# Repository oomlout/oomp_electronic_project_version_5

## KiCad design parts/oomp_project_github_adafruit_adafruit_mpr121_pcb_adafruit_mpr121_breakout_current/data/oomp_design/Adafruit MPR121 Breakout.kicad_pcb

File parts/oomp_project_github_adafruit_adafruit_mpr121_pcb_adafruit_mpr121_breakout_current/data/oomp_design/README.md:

# OOMP KiCad design copy

Open `Adafruit MPR121 Breakout.kicad_pro` (or the `.kicad_pcb` / `.kicad_sch`) in KiCad. Local OOMP libraries are under `libraries/`. Original inputs are preserved in [../original/](../original/).

Only verified unchanged installed KiCad defaults were renamed. Modified, custom, unmatched and unavailable items remain unchanged. Soldering variants are never swapped during conversion. Existing pad coordinates, nets and UUIDs are preserved.

See [conversion_report.yaml](conversion_report.yaml) for every conversion and skip. Copy this directory before editing; regeneration refuses to overwrite edited design files.

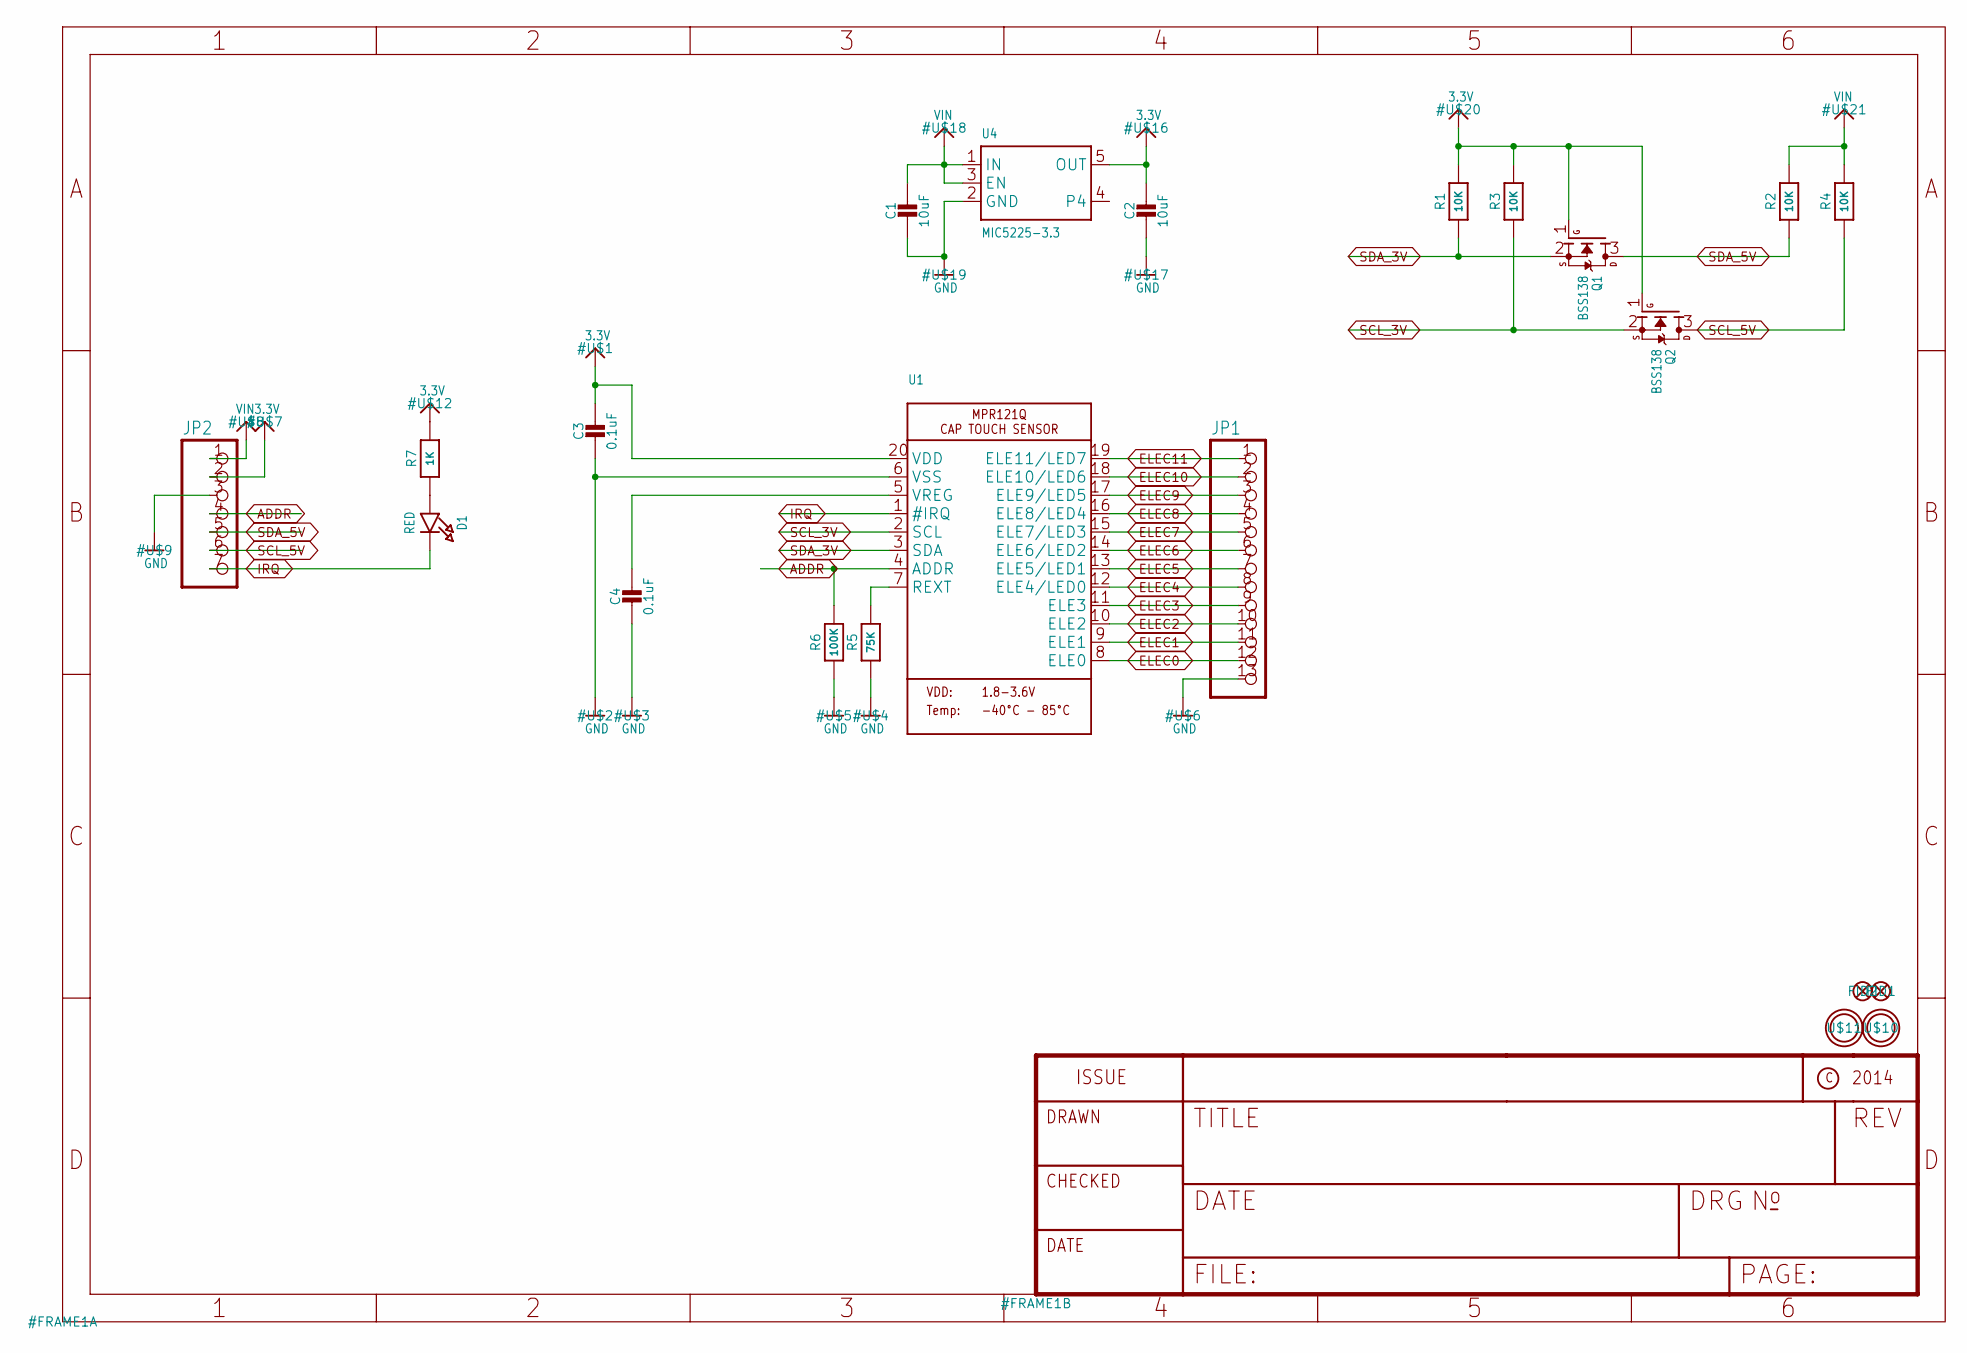
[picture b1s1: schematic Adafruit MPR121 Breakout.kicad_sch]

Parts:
C1, C2: 10uF; 0805-NO
C3: 0.1uF; 0805_10MGAP
C4: 0.1uF; 0805-NO
D1: RED; CHIPLED_0805_NOOUTLINE
FID1, FID2: FIDUCIAL""; FIDUCIAL_1MM
JP1: HEADER-1X13; 1X13_ROUND_70
JP2: HEADER-1X770MIL; 1X07_ROUND_70
Q1, Q2: BSS138; SOT23-WIDE
R1, R2, R3, R4: 10K; 0805-NO
R5: 75K; 0805-NO
R6: 100K; 0805-NO
R7: 1K; 0805-NO
U1: MPR121Q; QFN20_3MM_NOTHERMAL
U4: MIC5225-3.3; SOT23-5
U$10, U$11: MOUNTINGHOLE2.5; MOUNTINGHOLE_2.5_PLATED

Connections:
3.3V: C2.1, C3.1, JP2.2, Q1.1 (G), Q2.1 (G), R1.2, R3.2, R7.2, U1.20 (VDD), U4.5 (OUT)
ADDR: JP2.4, R6.2, U1.4 (ADDR)
ELEC0: JP1.12, U1.8 (ELE0)
ELEC1: JP1.11, U1.9 (ELE1)
ELEC2: JP1.10, U1.10 (ELE2)
ELEC3: JP1.9, U1.11 (ELE3)
ELEC4: JP1.8, U1.12 (ELE4/LED0)
ELEC5: JP1.7, U1.13 (ELE5/LED1)
ELEC6: JP1.6, U1.14 (ELE6/LED2)
ELEC7: JP1.5, U1.15 (ELE7/LED3)
ELEC8: JP1.4, U1.16 (ELE8/LED4)
ELEC9: JP1.3, U1.17 (ELE9/LED5)
ELEC10: JP1.2, U1.18 (ELE10/LED6)
ELEC11: JP1.1, U1.19 (ELE11/LED7)
GND: C1.2, C2.2, C3.2, C4.2, JP1.13, JP2.3, R5.1, R6.1, U1.6 (VSS), U4.2 (GND)
IRQ: D1.C, JP2.7, U1.1 (#IRQ)
unnamed: D1.A, R7.1
unnamed: C4.1, U1.5 (VREG)
unnamed: R5.2, U1.7 (REXT)
SCL_3V: Q2.2 (S), R3.1, U1.2 (SCL)
SCL_5V: JP2.6, Q2.3 (D), R4.1
SDA_3V: Q1.2 (S), R1.1, U1.3 (SDA)
SDA_5V: JP2.5, Q1.3 (D), R2.1
VIN: C1.1, JP2.1, R2.2, R4.2, U4.1 (IN), U4.3 (EN)

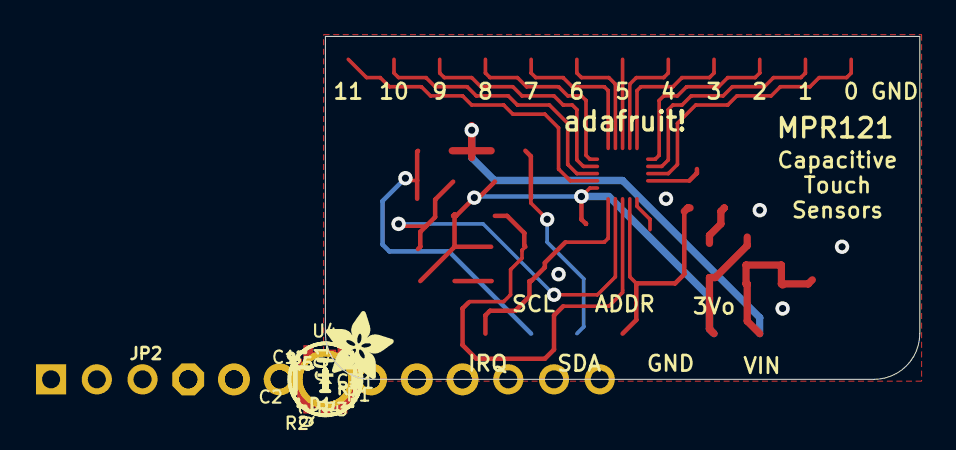
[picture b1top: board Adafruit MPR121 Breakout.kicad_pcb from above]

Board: 2 copper layers, 33.0 x 19.1 mm, 23 parts (0 on the bottom side), 24 nets.

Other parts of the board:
U$14: ADAFRUIT_3.5MM

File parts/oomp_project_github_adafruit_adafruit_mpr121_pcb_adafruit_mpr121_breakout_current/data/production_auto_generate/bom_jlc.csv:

Comment,Designator,Footprint,LCSC Part #
,JP2,Adafruit MPR121 Breakout-import-fps:1X07_ROUND_70,C7501585
,JP1,Adafruit MPR121 Breakout-import-fps:1X13_ROUND_70,C2894936
,U$14,Adafruit MPR121 Breakout-import-fps:ADAFRUIT_3.5MM,
,U1,Adafruit MPR121 Breakout-import-fps:QFN20_3MM_NOTHERMAL,
0.1uF,C4,Adafruit MPR121 Breakout-import-fps:0805-NO,
0.1uF,C3,Adafruit MPR121 Breakout-import-fps:0805_10MGAP,
100K,R6,Adafruit MPR121 Breakout-import-fps:0805-NO,C149504
10K,"R1,R2,R3,R4",Adafruit MPR121 Breakout-import-fps:0805-NO,C17414
10uF,"C1,C2",Adafruit MPR121 Breakout-import-fps:0805-NO,
1K,R7,Adafruit MPR121 Breakout-import-fps:0805-NO,C17513
75K,R5,Adafruit MPR121 Breakout-import-fps:0805-NO,C17819
BSS138,"Q1,Q2",Adafruit MPR121 Breakout-import-fps:SOT23-WIDE,C52895
MIC5225-3.3,U4,Adafruit MPR121 Breakout-import-fps:SOT23-5,
RED,D1,Adafruit MPR121 Breakout-import-fps:CHIPLED_0805_NOOUTLINE,

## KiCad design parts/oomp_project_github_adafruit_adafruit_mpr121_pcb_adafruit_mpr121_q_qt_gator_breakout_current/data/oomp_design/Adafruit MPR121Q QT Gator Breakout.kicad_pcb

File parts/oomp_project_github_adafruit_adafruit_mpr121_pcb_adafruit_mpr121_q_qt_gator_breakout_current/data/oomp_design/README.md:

# OOMP KiCad design copy

Open `Adafruit MPR121Q QT Gator Breakout.kicad_pro` (or the `.kicad_pcb` / `.kicad_sch`) in KiCad. Local OOMP libraries are under `libraries/`. Original inputs are preserved in [../original/](../original/).

Only verified unchanged installed KiCad defaults were renamed. Modified, custom, unmatched and unavailable items remain unchanged. Soldering variants are never swapped during conversion. Existing pad coordinates, nets and UUIDs are preserved.

See [conversion_report.yaml](conversion_report.yaml) for every conversion and skip. Copy this directory before editing; regeneration refuses to overwrite edited design files.

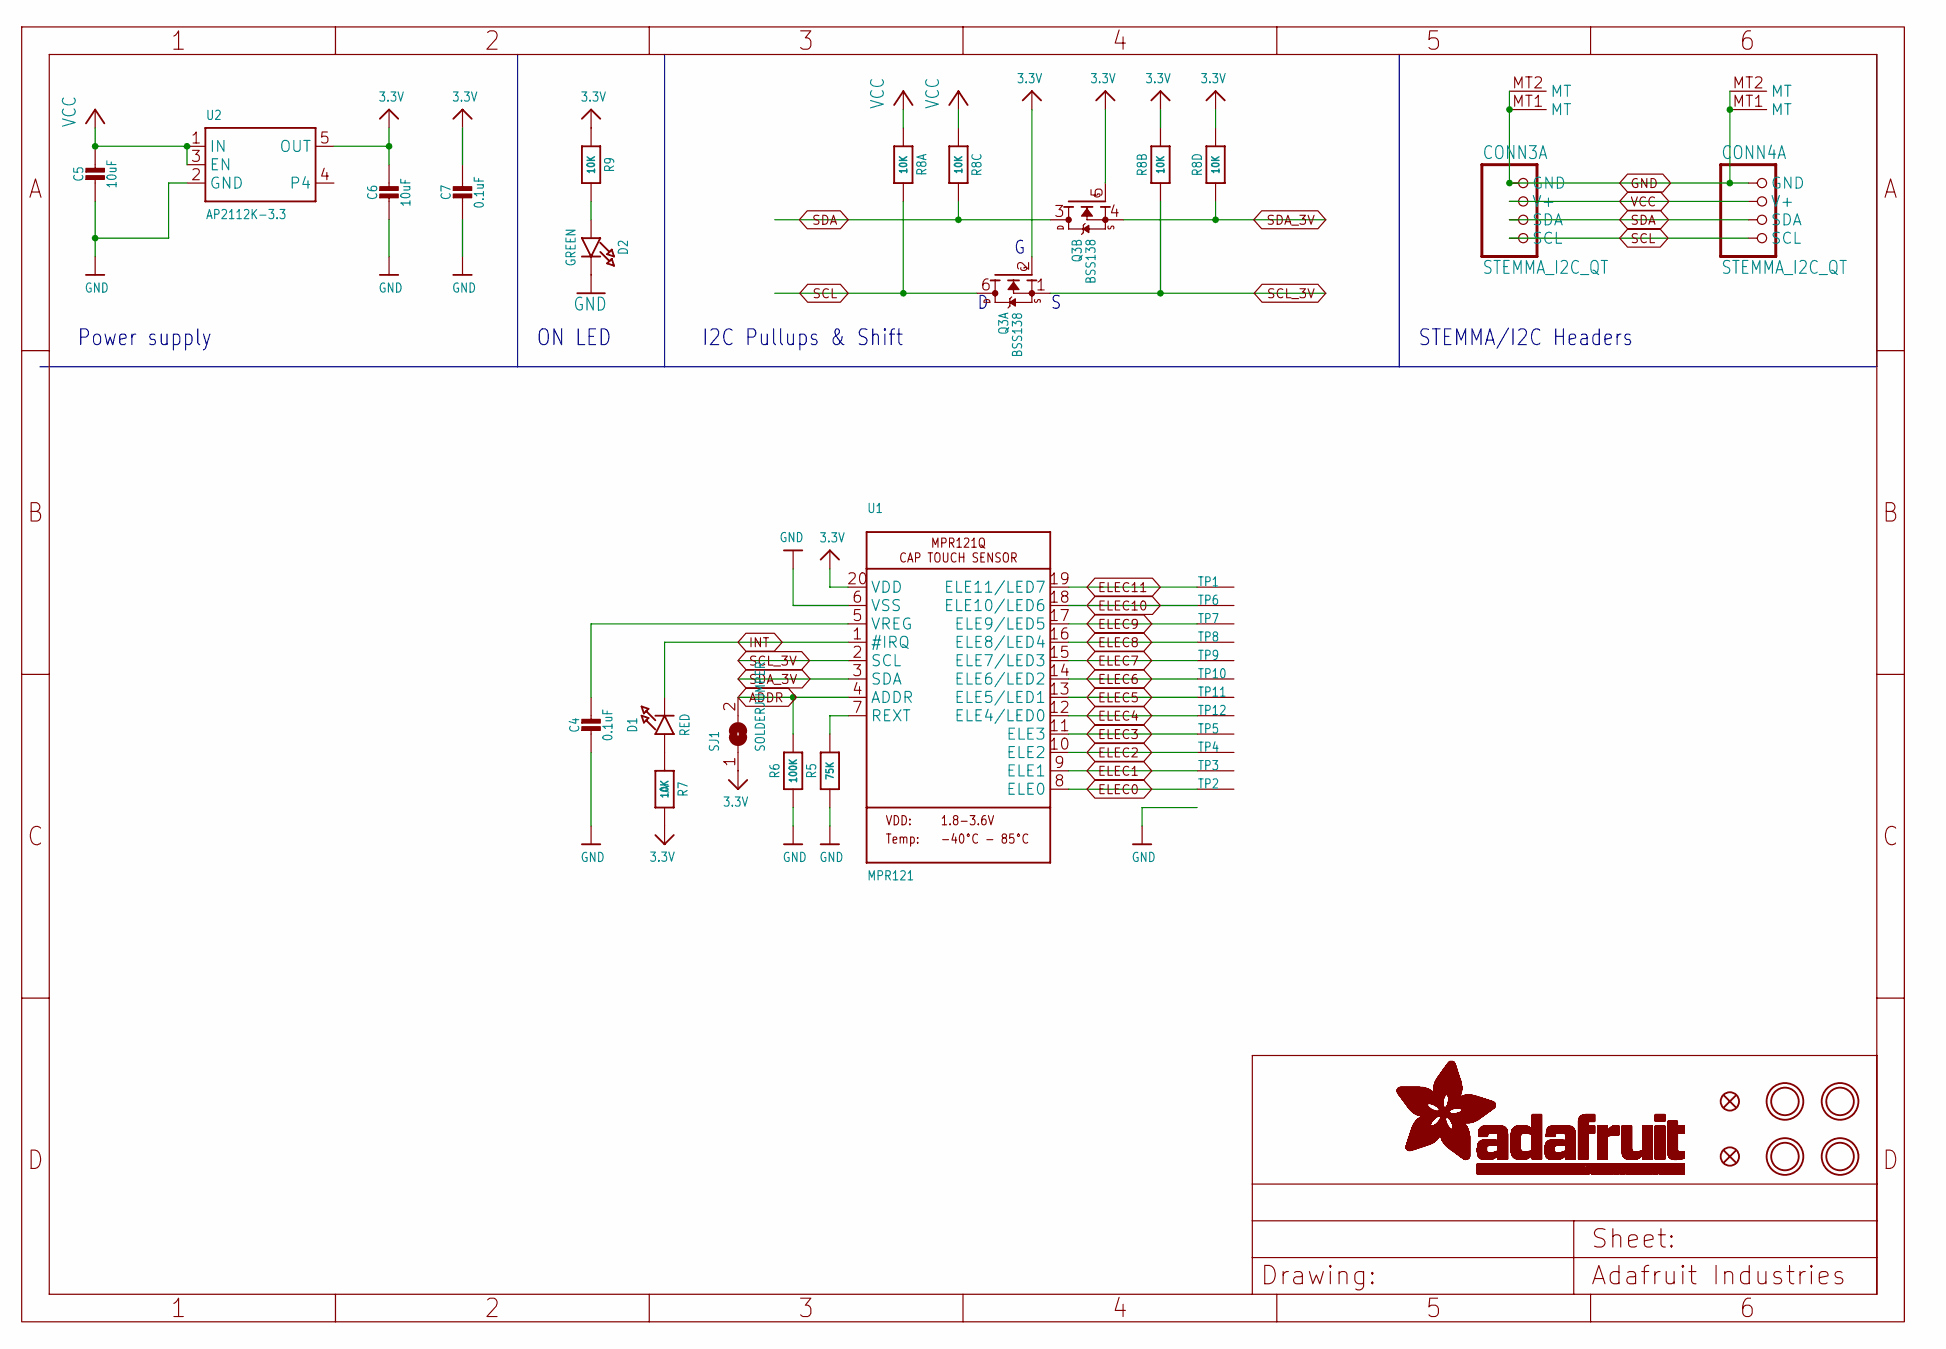
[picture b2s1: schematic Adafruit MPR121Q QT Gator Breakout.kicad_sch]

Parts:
C4, C7: 0.1uF; 0603-NO
C5, C6: 10uF; 0805-NO
CONN3, CONN4: STEMMA_I2C_QT; JST_SH4
D1: RED; CHIPLED_0603_NOOUTLINE
D2: GREEN; CHIPLED_0603_NOOUTLINE
FID3, FID4: FIDUCIAL_1MM
Q3: BSS138; SOT363
R5: 75K; 0603-NO
R6: 100K; 0603-NO
R7, R9: 10K; 0603-NO
R8: 10K; RESPACK_4X0603
SJ1: SOLDERJUMPER; SOLDERJUMPER_ARROW_NOPASTE
TP1, TP2, TP3, TP4, TP5, TP6, TP7, TP8, TP9, TP10, TP11, TP12: SEWTAPPCB_ALLIGATOR; PCB_ALLI
U1: MPR121; QFN20_3MM_NOTHERMAL
U2: AP2112K-3.3; SOT23-5
U$7, U$8, U$34, U$35: MOUNTINGHOLE2.5; MOUNTINGHOLE_2.5_PLATED

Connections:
3.3V: C6.1, C7.1, Q3.2 (G), Q3.5 (G), R7.2, R8.2 (1), R8.4 (1), R9.1, SJ1.1, U1.20 (VDD), U2.5 (OUT)
ADDR: R6.2, SJ1.2, U1.4 (ADDR)
ELEC0: TP2.P$1, U1.8 (ELE0)
ELEC1: TP3.P$1, U1.9 (ELE1)
ELEC2: TP4.P$1, U1.10 (ELE2)
ELEC3: TP5.P$1, U1.11 (ELE3)
ELEC4: TP12.P$1, U1.12 (ELE4/LED0)
ELEC5: TP11.P$1, U1.13 (ELE5/LED1)
ELEC6: TP10.P$1, U1.14 (ELE6/LED2)
ELEC7: TP9.P$1, U1.15 (ELE7/LED3)
ELEC8: TP8.P$1, U1.16 (ELE8/LED4)
ELEC9: TP7.P$1, U1.17 (ELE9/LED5)
ELEC10: TP6.P$1, U1.18 (ELE10/LED6)
ELEC11: TP1.P$1, U1.19 (ELE11/LED7)
GND: C4.2, C5.2, C6.2, C7.2, CONN3.1 (GND), CONN3.MT1 (MT), CONN3.MT2 (MT), CONN4.1 (GND), CONN4.MT1 (MT), CONN4.MT2 (MT), D2.C, R5.1, R6.1, U1.6 (VSS), U2.2 (GND)
INT: D1.C, U1.1 (#IRQ)
unnamed: D1.A, R7.1
unnamed: C4.1, U1.5 (VREG)
unnamed: R5.2, U1.7 (REXT)
unnamed: D2.A, R9.2
SCL: CONN3.4 (SCL), CONN4.4 (SCL), Q3.6 (D), R8.8 (2)
SCL_3V: Q3.1 (S), R8.7 (2), U1.2 (SCL)
SDA: CONN3.3 (SDA), CONN4.3 (SDA), Q3.3 (D), R8.6 (2)
SDA_3V: Q3.4 (S), R8.5 (2), U1.3 (SDA)
VCC: C5.1, CONN3.2 (V+), CONN4.2 (V+), R8.1, R8.3 (1), U2.1 (IN), U2.3 (EN)

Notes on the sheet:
ON LED
I2C Pullups & Shift
STEMMA/I2C Headers
Power supply

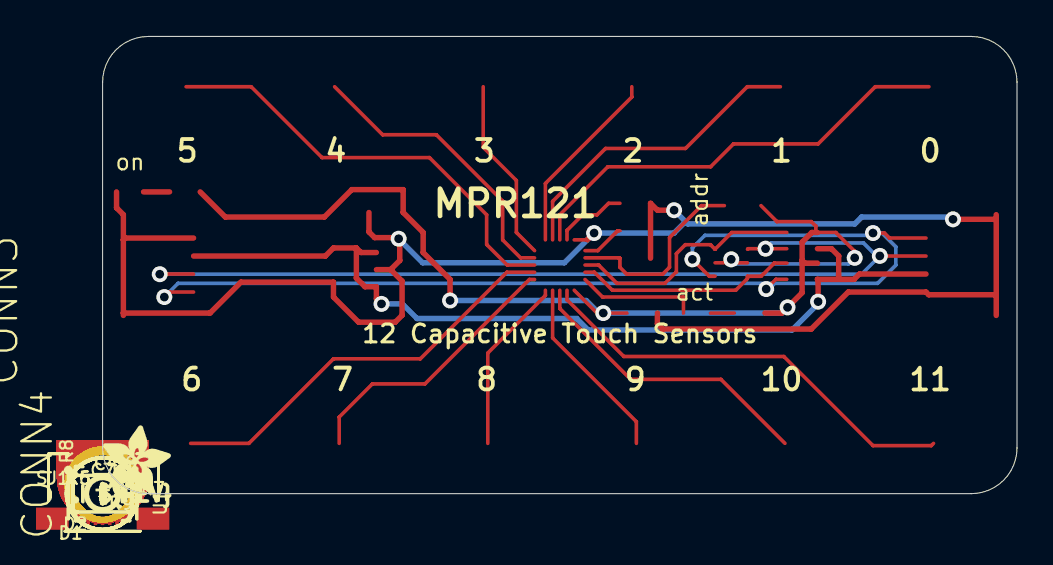
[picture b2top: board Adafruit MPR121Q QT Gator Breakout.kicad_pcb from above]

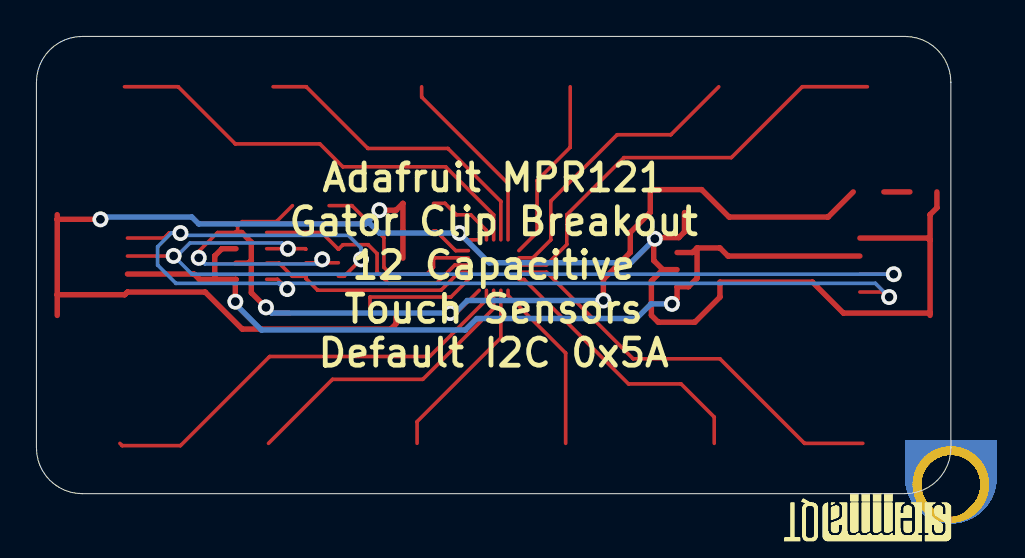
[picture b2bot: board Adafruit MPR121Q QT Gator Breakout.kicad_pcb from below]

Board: 2 copper layers, 50.8 x 25.4 mm, 39 parts (2 on the bottom side), 25 nets.

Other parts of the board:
U$10: PCBFEAT-REV-040
U$37: ADAFRUIT_3.5MM
U$39, U$40: STEMMAQT

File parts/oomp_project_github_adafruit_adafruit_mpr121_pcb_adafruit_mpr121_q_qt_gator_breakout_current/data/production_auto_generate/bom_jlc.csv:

Comment,Designator,Footprint,LCSC Part #
,U$37,Adafruit MPR121Q QT Gator Breakout-import-fps:ADAFRUIT_3.5MM,
,U$10,Adafruit MPR121Q QT Gator Breakout-import-fps:PCBFEAT-REV-040,
,"U$39,U$40",Adafruit MPR121Q QT Gator Breakout-import-fps:STEMMAQT,
0.1uF,"C4,C7",Adafruit MPR121Q QT Gator Breakout-import-fps:0603-NO,C14663
100K,R6,Adafruit MPR121Q QT Gator Breakout-import-fps:0603-NO,C25803
10K,"R7,R9",Adafruit MPR121Q QT Gator Breakout-import-fps:0603-NO,C98220
10K,R8,Adafruit MPR121Q QT Gator Breakout-import-fps:RESPACK_4X0603,C98220
10uF,"C5,C6",Adafruit MPR121Q QT Gator Breakout-import-fps:0805-NO,
75K,R5,Adafruit MPR121Q QT Gator Breakout-import-fps:0603-NO,C2907067
AP2112K-3.3,U2,Adafruit MPR121Q QT Gator Breakout-import-fps:SOT23-5,
BSS138,Q3,Adafruit MPR121Q QT Gator Breakout-import-fps:SOT363,
GREEN,D2,Adafruit MPR121Q QT Gator Breakout-import-fps:CHIPLED_0603_NOOUTLINE,
MPR121,U1,Adafruit MPR121Q QT Gator Breakout-import-fps:QFN20_3MM_NOTHERMAL,
RED,D1,Adafruit MPR121Q QT Gator Breakout-import-fps:CHIPLED_0603_NOOUTLINE,
STEMMA_I2C_QT,"CONN3,CONN4",Adafruit MPR121Q QT Gator Breakout-import-fps:JST_SH4,C160404

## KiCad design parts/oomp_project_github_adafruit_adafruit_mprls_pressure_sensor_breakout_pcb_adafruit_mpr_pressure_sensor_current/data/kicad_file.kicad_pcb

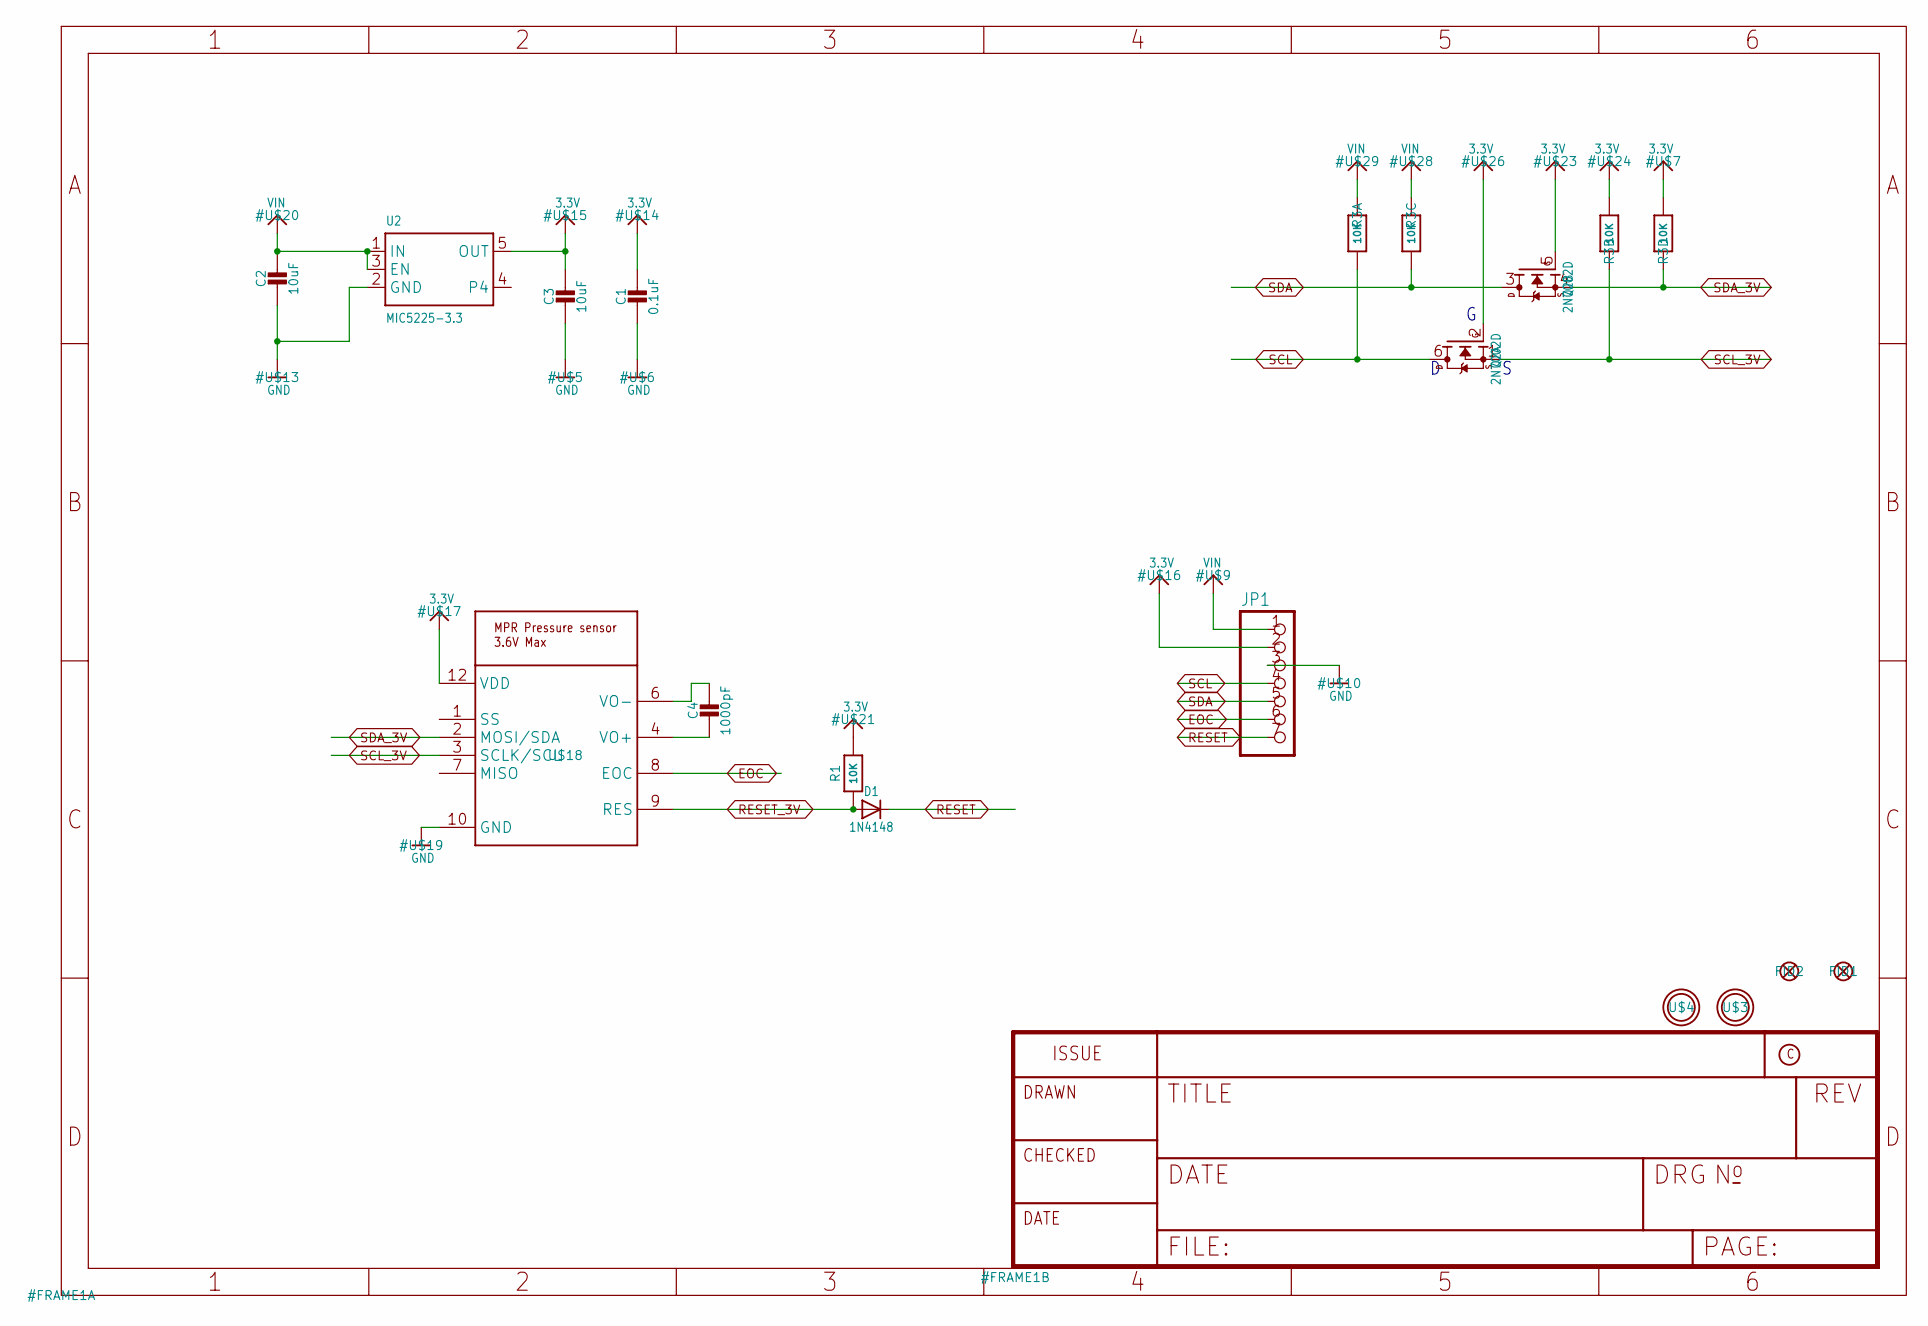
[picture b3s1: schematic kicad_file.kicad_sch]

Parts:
C1: 0.1uF; 0603-NO
C2, C3: 10uF; 0805-NO
C4: 1000pF; 0603-NO
D1: 1N4148; SOD-323
FID1, FID2: FIDUCIAL_1MM
JP1: HEADER-1X770MIL; 1X07_ROUND_70
Q2: 2N7002D; SOT363
R1: 10K; 0603-NO
R3: 10K; RESPACK_4X0603
U2: MIC5225-3.3; SOT23-5
U$3, U$4: MOUNTINGHOLE2.5; MOUNTINGHOLE_2.5_PLATED
U$18: MPR_SERIES_I2C_PRESSURE

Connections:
3.3V: C1.1, C3.1, JP1.2, Q2.2 (G), Q2.5 (G), R1.2, R3.2 (1), R3.4 (1), U2.5 (OUT), U$18.12 (VDD)
EOC: JP1.6, U$18.8 (EOC)
GND: C1.2, C2.2, C3.2, JP1.3, U2.2 (GND), U$18.10 (GND)
unnamed: C4.2, U$18.4 (VO+)
unnamed: C4.1, U$18.6 (VO-)
RESET: D1.C, JP1.7
RESET_3V: D1.A, R1.1, U$18.9 (RES)
SCL: JP1.4, Q2.6 (D), R3.8 (2)
SCL_3V: Q2.1 (S), R3.7 (2), U$18.3 (SCLK/SCL)
SDA: JP1.5, Q2.3 (D), R3.6 (2)
SDA_3V: Q2.4 (S), R3.5 (2), U$18.2 (MOSI/SDA)
VIN: C2.1, JP1.1, R3.1, R3.3 (1), U2.1 (IN), U2.3 (EN)

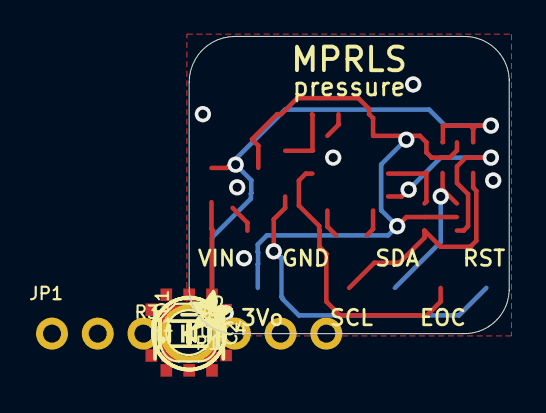
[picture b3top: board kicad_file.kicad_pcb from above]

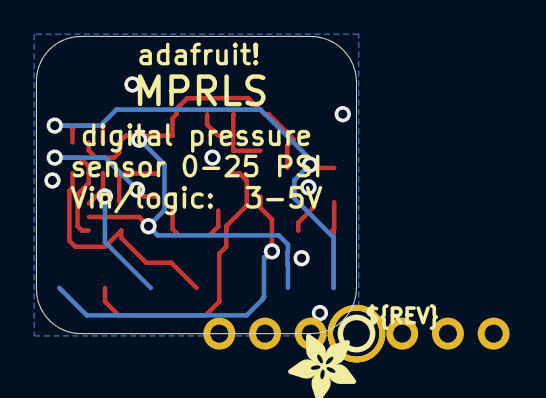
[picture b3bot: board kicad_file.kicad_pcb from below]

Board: 2 copper layers, 17.8 x 16.5 mm, 18 parts (2 on the bottom side), 12 nets.

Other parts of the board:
U$1: ADAFRUIT_3.5MM
U$8: ADAFRUIT_2.5MM
U$27: PCBFEAT-REV-040

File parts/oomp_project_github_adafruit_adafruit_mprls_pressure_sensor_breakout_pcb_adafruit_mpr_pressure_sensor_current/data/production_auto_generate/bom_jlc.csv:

Comment,Designator,Footprint,LCSC Part #
,JP1,Adafruit MPR pressure sensor-import-fps:1X07_ROUND_70,C7501585
,U$8,Adafruit MPR pressure sensor-import-fps:ADAFRUIT_2.5MM,
,U$1,Adafruit MPR pressure sensor-import-fps:ADAFRUIT_3.5MM,
,U$27,Adafruit MPR pressure sensor-import-fps:PCBFEAT-REV-040,
0.1uF,C1,Adafruit MPR pressure sensor-import-fps:0603-NO,C14663
1000pF,C4,Adafruit MPR pressure sensor-import-fps:0603-NO,
10K,R1,Adafruit MPR pressure sensor-import-fps:0603-NO,C98220
10K,R3,Adafruit MPR pressure sensor-import-fps:RESPACK_4X0603,C98220
10uF,"C2,C3",Adafruit MPR pressure sensor-import-fps:0805-NO,
1N4148,D1,Adafruit MPR pressure sensor-import-fps:SOD-323,
2N7002D,Q2,Adafruit MPR pressure sensor-import-fps:SOT363,
MIC5225-3.3,U2,Adafruit MPR pressure sensor-import-fps:SOT23-5,
MPR_SERIES_I2C_PRESSURE,U$18,Adafruit MPR pressure sensor-import-fps:MPR_SERIES_I2C_PRESSURE,
